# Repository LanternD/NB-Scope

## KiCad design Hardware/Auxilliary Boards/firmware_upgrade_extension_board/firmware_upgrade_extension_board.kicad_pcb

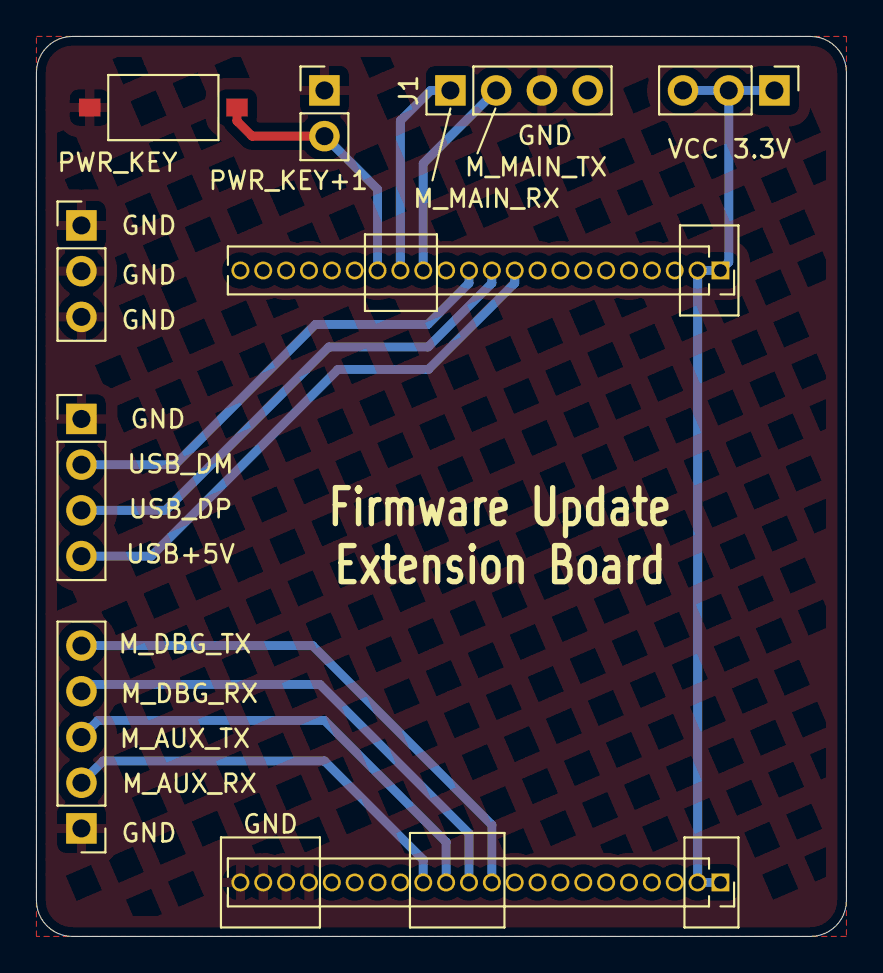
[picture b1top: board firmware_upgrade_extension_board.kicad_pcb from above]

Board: 2 copper layers, 45.0 x 50.0 mm, 9 parts (0 on the bottom side), 12 nets.

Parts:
J1: MAIN_UART_CONN; PinHeader_1x04_P2.54mm_Vertical
J2: Left_Conn; PinSocket_1x22_P1.27mm_Vertical
J3: Right_Conn; PinSocket_1x22_P1.27mm_Vertical
J4: PWR_KEY_TO_GND_CONN; PinHeader_1x02_P2.54mm_Vertical
J5: VCC_CONN; PinHeader_1x03_P2.54mm_Vertical
J6: GND_CONN; PinHeader_1x03_P2.54mm_Vertical
J7: DBG_UART_CONN; PinHeader_1x05_P2.54mm_Vertical
J8: USB_CONN; PinHeader_1x04_P2.54mm_Vertical
SW1: PWR_KEY_TO_GND_BTN; SMD_Switch

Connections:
+3V3: J2.1, J2.2, J3.1, J3.2, J5.1, J5.2, J5.3
/M_AUX_UART_Rx: J3.14, J7.2
/M_AUX_UART_Tx: J3.13, J7.3
/M_DBG_UART_Rx: J3.12, J7.4
/M_DBG_UART_TX: J3.11, J7.5
/M_MAIN_UART_Rx: J1.1, J2.15
/M_MAIN_UART_Tx: J1.2, J2.14
/M_PWRKEY: J2.16, J4.2, SW1.2
/M_USB_DM: J2.12, J8.2
/M_USB_DP: J2.11, J8.3
/M_USB_VBUS: J2.10, J8.4
GND: J1.3, J3.19, J3.20, J3.21, J3.22, J4.1, J6.1, J6.2, J6.3, J7.1, J8.1, SW1.1

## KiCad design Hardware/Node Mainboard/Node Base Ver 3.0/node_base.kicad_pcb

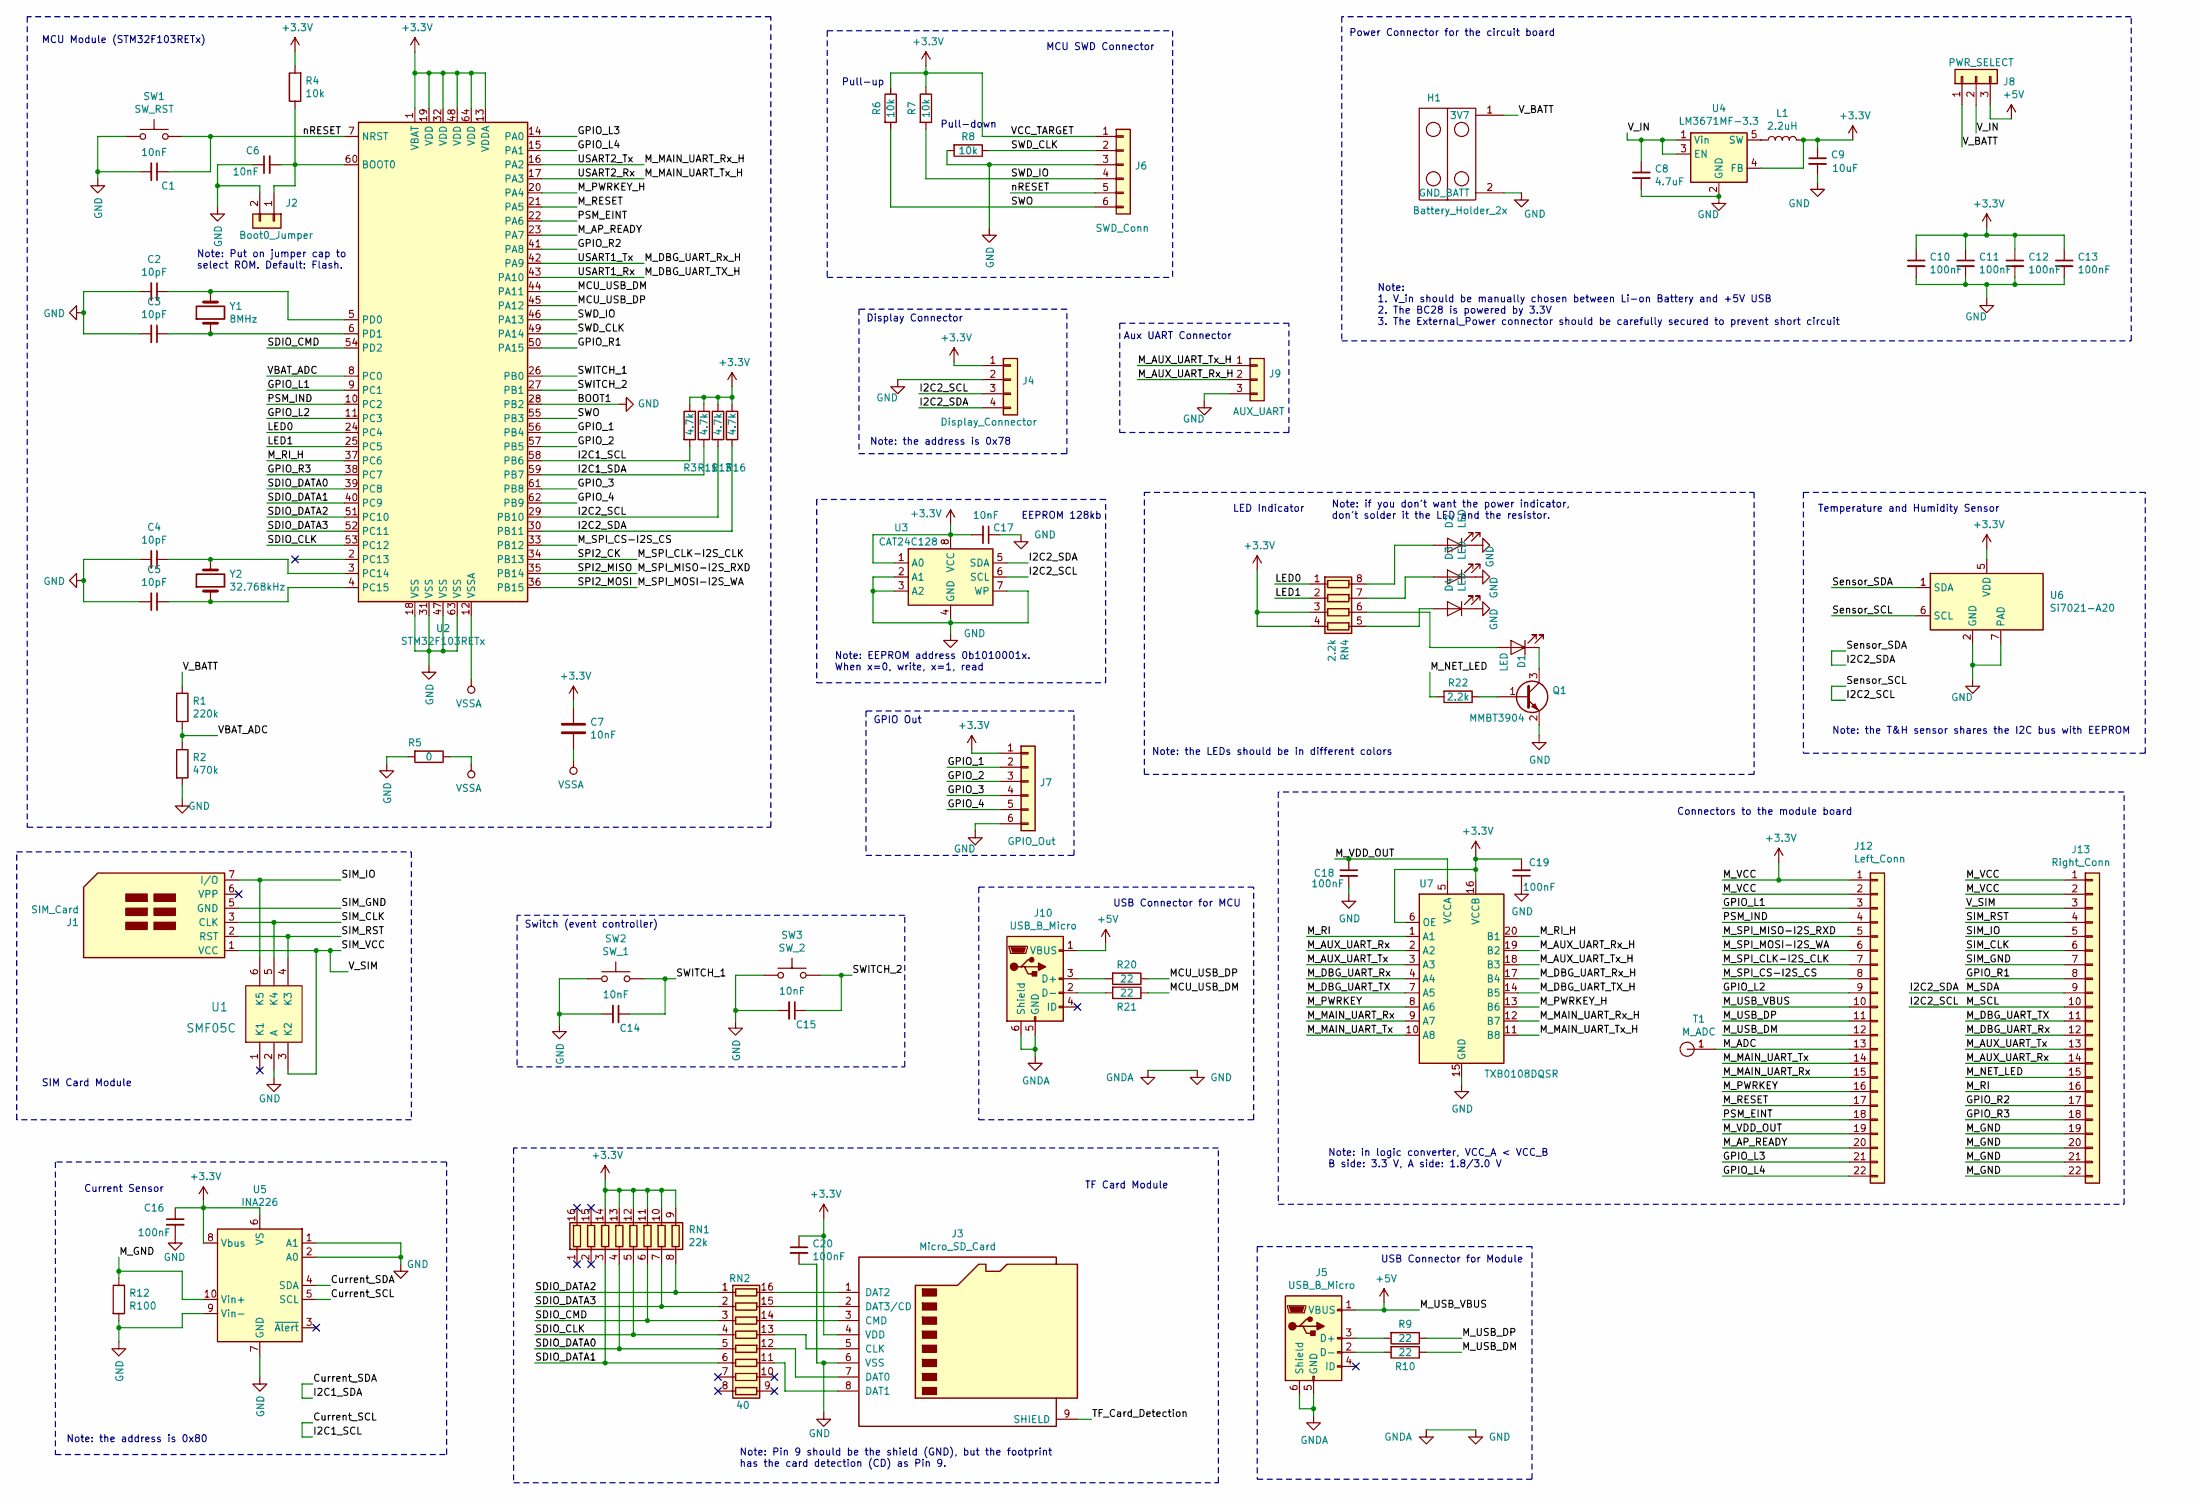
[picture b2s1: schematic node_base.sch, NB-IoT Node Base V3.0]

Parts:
C1, C6, C7, C14, C15, C17: 10nF; C_0603_1608Metric
C2, C3, C4, C5: 10pF; C_0603_1608Metric
C8: 4.7uF; C_1210_3225Metric
C9: 10uF; CP_Elec_4x5.4
C10, C11, C12, C13, C16, C18, C19, C20: 100nF; C_0603_1608Metric
D1, D2, D3, D4: LED; LED_0805_2012Metric
H1: Battery_Holder_2x; 18650_Battery_Holder_2x
J1: SIM_Card; Nano Sim Socket 1.1H, 6P
J2: Boot0_Jumper; PinHeader_1x02_P1.27mm_Vertical
J3: Micro_SD_Card; TF_Card_Socket
J4: Display_Connector; PinSocket_1x04_P1.27mm_Vertical
J5, J10: USB_B_Micro; USB_Micro-B_Molex-105017-0001
J6: SWD_Conn; PinSocket_1x06_P1.27mm_Vertical
J7: GPIO_Out; PinSocket_1x06_P1.27mm_Vertical
J8: PWR_SELECT; PinHeader_1x03_P2.54mm_Vertical
J9: AUX_UART; PinSocket_1x03_P1.27mm_Vertical
J12: Left_Conn; PinHeader_1x22_P1.27mm_Vertical
J13: Right_Conn; PinHeader_1x22_P1.27mm_Vertical
L1: 2.2uH; L_7.3x7.3_H4.5
Q1: MMBT3904; SOT-23
R1: 220k; R_0603_1608Metric
R2: 470k; R_0603_1608Metric
R3, R11, R13, R16: 4.7k; R_0603_1608Metric
R4, R6, R7, R8: 10k; R_0603_1608Metric
R5: 0; R_0603_1608Metric
R9, R10, R20, R21: 22; R_0603_1608Metric
R12: R100; R_1206_3216Metric
R22: 2.2k; R_0603_1608Metric_Pad1.05x0.95mm_HandSolder
RN1: 22k; R_Array_Convex_8x0602
RN2: 40; R_Array_Convex_8x0602
RN4: 2.2k; R_Array_Convex_4x0603
SW1: SW_RST; SW_SPST_FSMSM
SW2: SW_1; SW_SPST_FSMSM
SW3: SW_2; SW_SPST_FSMSM
T1: M_ADC; test_pad
U1: SMF05C
U2: STM32F103RETx; LQFP-64_10x10mm_P0.5mm
U3: CAT24C128; SOIC-8_3.9x4.9mm_P1.27mm
U4: LM3671MF-3.3; TSOT-23-5
U5: INA226; VSSOP-10_3x3mm_P0.5mm
U6: Si7021-A20; DFN-6-1EP_3x3mm_P1mm_EP1.5x2.4mm
U7: TXB0108DQSR; USON-20_2x4mm_P0.4mm
Y1: 8MHz; Crystal_SMD_5032-2Pin_5.0x3.2mm
Y2: 32.768kHz; Crystal_SMD_3215-2Pin_3.2x1.5mm

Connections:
+3V3: C7.1, C9.1, C10.1, C11.1, C12.1, C13.1, C16.1, C17.2, C19.2, C20.1, J3.4 (VDD), J4.1, J6.1, J7.1, J12.1, J12.2, J13.1, J13.2, L1.2, R3.1, R4.2, R6.1, R7.1, R11.1, R13.1, R16.1, RN1.9 (R8.2), RN1.10 (R7.2), RN1.11 (R6.2), RN1.12 (R5.2), RN1.13 (R4.2), RN1.14 (R3.2), RN4.3 (R3.1), RN4.4 (R4.1), U2.1 (VBAT), U2.13 (VDDA), U2.19 (VDD), U2.32 (VDD), U2.48 (VDD), U2.64 (VDD), U3.1 (A0), U3.8 (VCC), U4.4 (FB), U5.6 (VS), U5.8 (Vbus), U6.5 (VDD), U7.6 (OE), U7.16 (VCCB)
+5V: J5.1 (VBUS), J8.3, J10.1 (VBUS), J12.10
/Current_SCL: R3.2, U2.58 (PB6), U5.5 (SCL)
/Current_SDA: R11.2, U2.59 (PB7), U5.4 (SDA)
/GPIO_2: J7.3, U2.57 (PB5)
/GPIO_3: J7.4, U2.61 (PB8)
/GPIO_4: J7.5, U2.62 (PB9)
/GPIO_L1: J12.3, U2.9 (PC1)
/GPIO_L2: J12.9, U2.11 (PC3)
/GPIO_L3: J12.21, U2.14 (PA0)
/GPIO_L4: J12.22, U2.15 (PA1)
/GPIO_R1: J13.8, U2.50 (PA15)
/GPIO_R2: J13.17, U2.41 (PA8)
/GPIO_R3: J13.18, U2.38 (PC7)
/I2C2_SCL: J4.3, J13.10, R13.2, U2.29 (PB10), U3.6 (SCL), U6.6 (SCL)
/I2C2_SDA: J4.4, J13.9, R16.2, U2.30 (PB11), U3.5 (SDA), U6.1 (SDA)
/LED0: RN4.1 (R1.1), U2.24 (PC4)
/LED1: RN4.2 (R2.1), U2.25 (PC5)
/MCU_USB_DM: R21.1, U2.44 (PA11)
/MCU_USB_DP: R20.1, U2.45 (PA12)
/M_ADC: J12.13, T1.1
/M_AP_READY: J12.20, U2.23 (PA7)
/M_AUX_UART_Rx: J13.14, U7.2 (A2)
/M_AUX_UART_Rx_H: J9.2, U7.19 (B2)
/M_AUX_UART_Tx: J13.13, U7.3 (A3)
/M_AUX_UART_Tx_H: J9.1, U7.18 (B3)
/M_DBG_UART_Rx: J13.12, U7.4 (A4)
/M_DBG_UART_Rx_H: U2.42 (PA9), U7.17 (B4)
/M_DBG_UART_TX: J13.11, U7.7 (A5)
/M_DBG_UART_TX_H: U2.43 (PA10), U7.14 (B5)
/M_GND: J13.19, J13.20, J13.21, J13.22, R12.1, U5.10 (Vin+)
/M_MAIN_UART_Rx: J12.15, U7.9 (A7)
/M_MAIN_UART_Rx_H: U2.16 (PA2), U7.12 (B7)
/M_MAIN_UART_Tx: J12.14, U7.10 (A8)
/M_MAIN_UART_Tx_H: U2.17 (PA3), U7.11 (B8)
/M_NET_LED: J13.15, R22.2
/M_PWRKEY: J12.16, U7.8 (A6)
/M_PWRKEY_H: U2.20 (PA4), U7.13 (B6)
/M_RESET: J12.17, U2.21 (PA5)
/M_RI: J13.16, U7.1 (A1)
/M_RI_H: U2.37 (PC6), U7.20 (B1)
/M_SPI_CLK-I2S_CLK: J12.7, U2.34 (PB13)
/M_SPI_CS-I2S_CS: J12.8, U2.33 (PB12)
/M_SPI_MISO-I2S_RXD: J12.5, U2.35 (PB14)
/M_SPI_MOSI-I2S_WA: J12.6, U2.36 (PB15)
/M_USB_DM: J12.12, R10.1
/M_USB_DP: J12.11, R9.1
/M_VDD_OUT: C18.1, J12.19, U7.5 (VCCA)
/PSM_EINT: J12.18, U2.22 (PA6)
/PSM_IND: J12.4, U2.10 (PC2)
/SDIO_CLK: RN1.5 (R5.1), RN2.4 (R4.1), U2.53 (PC12)
/SDIO_CMD: RN1.6 (R6.1), RN2.3 (R3.1), U2.54 (PD2)
/SDIO_DATA0: RN1.4 (R4.1), RN2.5 (R5.1), U2.39 (PC8)
/SDIO_DATA1: RN1.3 (R3.1), RN2.6 (R6.1), U2.40 (PC9)
/SDIO_DATA2: RN1.8 (R8.1), RN2.1 (R1.1), U2.51 (PC10)
/SDIO_DATA3: RN1.7 (R7.1), RN2.2 (R2.1), U2.52 (PC11)
/SIM_CLK: J1.3 (CLK), J13.6, U1.5 (K4)
/SIM_GND: J1.5 (GND), J13.7
/SIM_IO: J1.7 (I/O), J13.5, U1.6 (K5)
/SIM_RST: J1.2 (RST), J13.4, U1.4 (K3)
/SIM_VCC: J1.1 (VCC), J13.3, U1.3 (K2)
/SWD_CLK: J6.2, R8.1, U2.49 (PA14)
/SWD_IO: J6.4, R7.2, U2.46 (PA13)
/SWITCH_1: C14.1, SW2.2, U2.26 (PB0)
/SWITCH_2: C15.1, SW3.2, U2.27 (PB1)
/SWO: J6.6, R6.2, U2.55 (PB3)
/VBAT_ADC: R1.2, R2.1, U2.8 (PC0)
/V_BATT: H1.1 (3V7), J8.1, R1.1
/V_IN: C8.1, J8.2, U4.1 (Vin), U4.3 (EN)
/nRESET: C1.1, J6.5, SW1.2, U2.7 (NRST)
GND: C1.2, C2.2, C3.2, C4.2, C5.2, C6.1, C8.2, C9.2, C10.2, C11.2, C12.2, C13.2, C14.2, C15.2, C16.2, C17.1, C18.2, C19.1, C20.2, D2.1 (K), D3.1 (K), D4.1 (K), H1.2 (GND_BATT), J2.2, J3.6 (VSS), J4.2, J5.5 (GND), J5.6 (Shield), J6.3, J7.6, J9.3, J10.5 (GND), J10.6 (Shield), Q1.2 (E), R2.2, R5.2, R8.2, R12.2, SW1.1, SW2.1, SW3.1, U1.2 (A), U2.18 (VSS), U2.28 (PB2), U2.31 (VSS), U2.47 (VSS), U2.63 (VSS), U3.2 (A1), U3.3 (A2), U3.4 (GND), U3.7 (WP), U4.2 (GND), U5.1 (A1), U5.2 (A0), U5.7 (GND), U5.9 (Vin-), U6.2 (GND), U6.7 (PAD), U7.15 (GND)
unnamed: C2.1, U2.5 (PD0), Y1.2
unnamed: C3.1, U2.6 (PD1), Y1.1
unnamed: C4.1, U2.3 (PC14), Y2.2
unnamed: C5.1, U2.4 (PC15), Y2.1
unnamed: C6.2, J2.1, R4.1, U2.60 (BOOT0)
unnamed: D1.1 (K), Q1.3 (C)
unnamed: D1.2 (A), RN4.6 (R3.2)
unnamed: D2.2 (A), RN4.8 (R1.2)
unnamed: D3.2 (A), RN4.7 (R2.2)
unnamed: D4.2 (A), RN4.5 (R4.2)
unnamed: J3.1 (DAT2), RN2.16 (R1.2)
unnamed: J3.2 (DAT3/CD), RN2.15 (R2.2)
unnamed: J3.3 (CMD), RN2.14 (R3.2)
unnamed: J3.5 (CLK), RN2.13 (R4.2)
unnamed: J3.7 (DAT0), RN2.12 (R5.2)
unnamed: J3.8 (DAT1), RN2.11 (R6.2)
unnamed: J5.2 (D-), R10.2
unnamed: J5.3 (D+), R9.2
unnamed: J10.2 (D-), R21.2
unnamed: J10.3 (D+), R20.2
unnamed: L1.1, U4.5 (SW)
unnamed: Q1.1 (B), R22.1
VSSA: C7.2, R5.1, U2.12 (VSSA)

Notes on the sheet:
Note: Put on jumper cap to select ROM. Default: Flash.
MCU Module (STM32F103RETx)
Power Connector for the circuit board
Note: 1. V_in should be manually chosen between Li-on Battery and +5V USB 2. The BC28 is powered by 3.3V 3. The External_Power connector should be carefully secured to prevent short circuit
Pull-down
Pull-up
MCU SWD Connector
EEPROM 128kb
Note: the LEDs should be in different colors
LED Indicator
Note: if you don’t want the power indicator, don’t solder it the LED and the resistor.
Note: the T&H sensor shares the I2C bus with EEPROM
Connectors to the module board
Current Sensor
SIM Card Module
Temperature and Humidity Sensor
Switch (event controller)
Note: Pin 9 should be the shield (GND), but the footprint has the card detection (CD) as Pin 9.
TF Card Module
Note: EEPROM address 0b1010001x. When x=0, write, x=1, read
Display Connector
Note: the address is 0x78
Note: the address is 0x80
Aux UART Connector
USB Connector for MCU
USB Connector for Module
GPIO Out
Note: in logic converter, VCC_A < VCC_B B side: 3.3 V, A side: 1.8/3.0 V

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
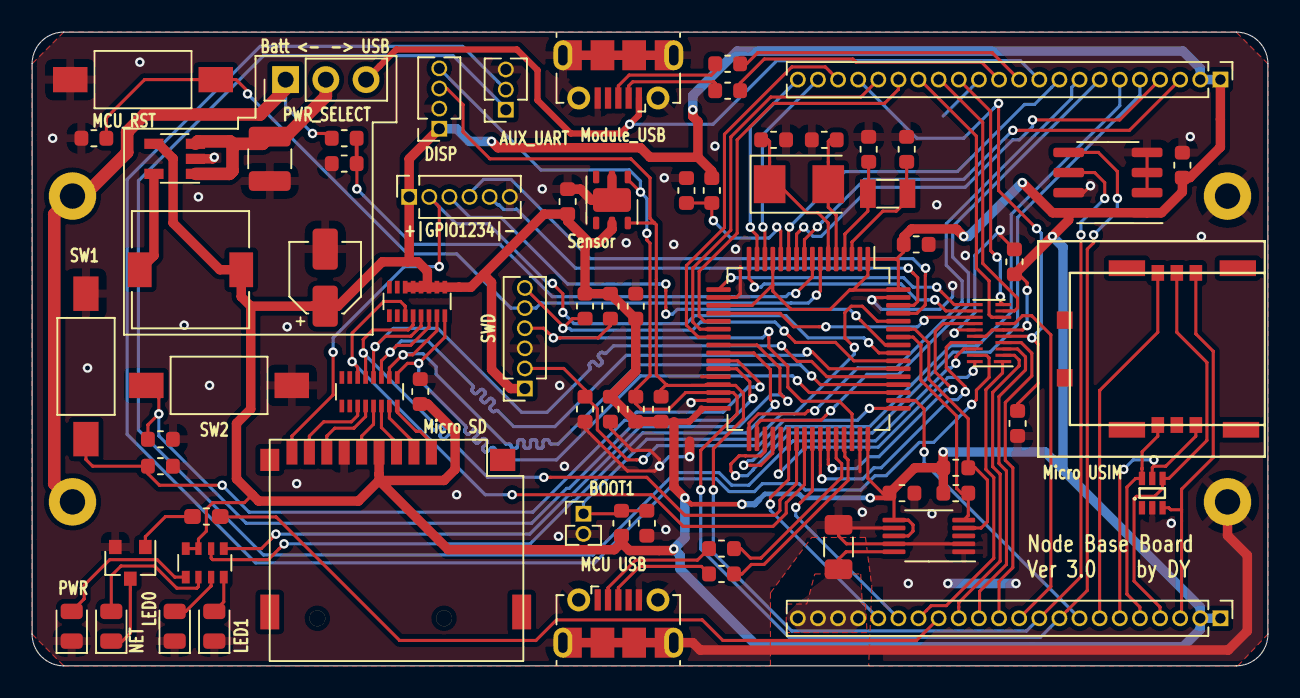
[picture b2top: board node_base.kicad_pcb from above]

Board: 2 copper layers, 78.0 x 40.0 mm, 72 parts (1 on the bottom side), 95 nets.

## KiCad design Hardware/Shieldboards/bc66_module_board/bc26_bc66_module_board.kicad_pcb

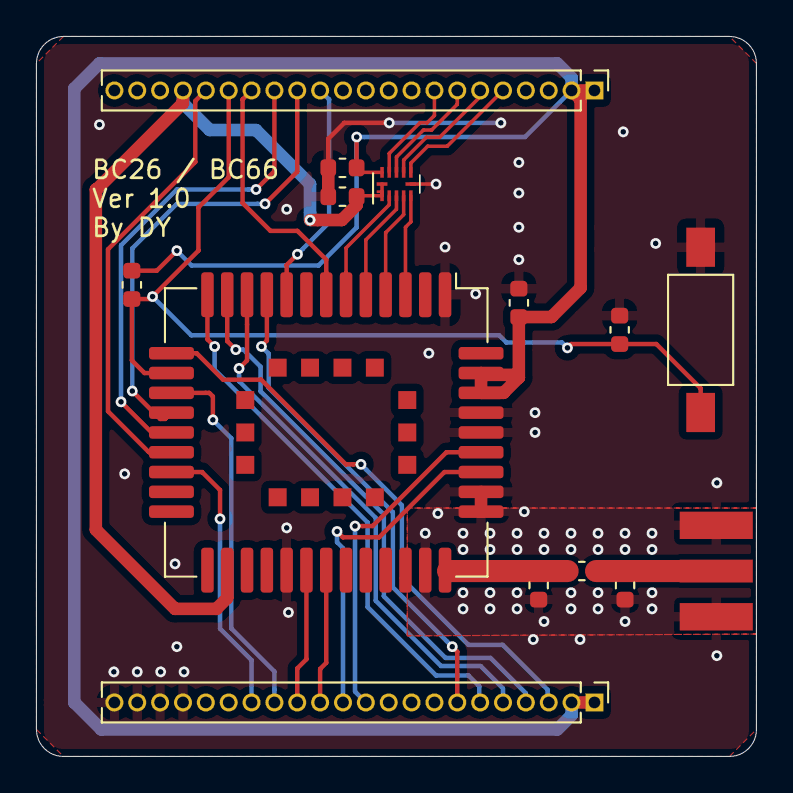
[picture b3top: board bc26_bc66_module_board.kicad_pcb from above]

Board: 2 copper layers, 40.0 x 40.0 mm, 14 parts (0 on the bottom side), 30 nets.

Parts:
C1, C2, C3, C4, C5, C7: 100nF; C_0603_1608Metric
J1: 1865; SMA_Antenna
J12: Left_Conn; PinHeader_1x22_P1.27mm_Vertical
J13: Right_Conn; PinHeader_1x22_P1.27mm_Vertical
R1: 0; R_0603_1608Metric
R11: 10k; R_0603_1608Metric
SW2: SW_Push; SW_SPST_FSMSM
U1: BC66; Quectel_BC66
U2: TXB0304RUT; Texas_R_PUQFN-N12

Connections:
+3V3: C1.1, C5.1, J12.1, J12.2, J13.1, J13.2, R11.2, U1.42, U1.43, U2.11
/B_SPI_CLK-I2S_CLK: J12.7, U2.9
/B_SPI_CS-I2S_CS: J12.8, U2.10
/B_SPI_MISO-I2S_RXD: J12.5, U2.7
/B_SPI_MOSI-I2S_WA: J12.6, U2.8
/M_ADC: J12.13, U1.9
/M_AUX_UART_Rx: J13.14, U1.28
/M_AUX_UART_Tx: J13.13, U1.29
/M_DBG_UART_Rx: J13.12, U1.38
/M_DBG_UART_TX: J13.11, U1.39
/M_MAIN_UART_Rx: J12.15, U1.18
/M_MAIN_UART_Tx: J12.14, U1.17
/M_NET_LED: J13.15, U1.16
/M_PWRKEY: J12.16, U1.7
/M_RESET: C7.1, J12.17, R11.1, SW2.2, U1.15
/M_RI: J13.16, U1.20
/M_SPI_CLK-I2S_CLK: U1.5, U2.3
/M_SPI_CS-I2S_CS: U1.6, U2.2
/M_SPI_MISO-I2S_RXD: U1.3, U2.5
/M_SPI_MOSI-I2S_WA: U1.4, U2.4
/M_VDD_OUT: C4.1, J12.19, U1.24, U2.1, U2.12
/PSM_EINT: J12.18, U1.19
/SIM_CLK: J13.6, U1.13
/SIM_GND: J13.7, U1.10
/SIM_IO: J13.5, U1.11
/SIM_RST: J13.4, U1.12
/V_SIM: J13.3, U1.14
GND: C1.2, C2.2, C3.2, C4.2, C5.2, C7.2, J1.GND1, J1.GND2, J1.GND3, J1.GND4, J13.19, J13.20, J13.21, J13.22, SW2.1, U1.1, U1.27, U1.34, U1.36, U1.37, U1.40, U1.41, U2.6
unnamed: C2.1, R1.2, U1.35
unnamed: C3.1, J1.P, R1.1

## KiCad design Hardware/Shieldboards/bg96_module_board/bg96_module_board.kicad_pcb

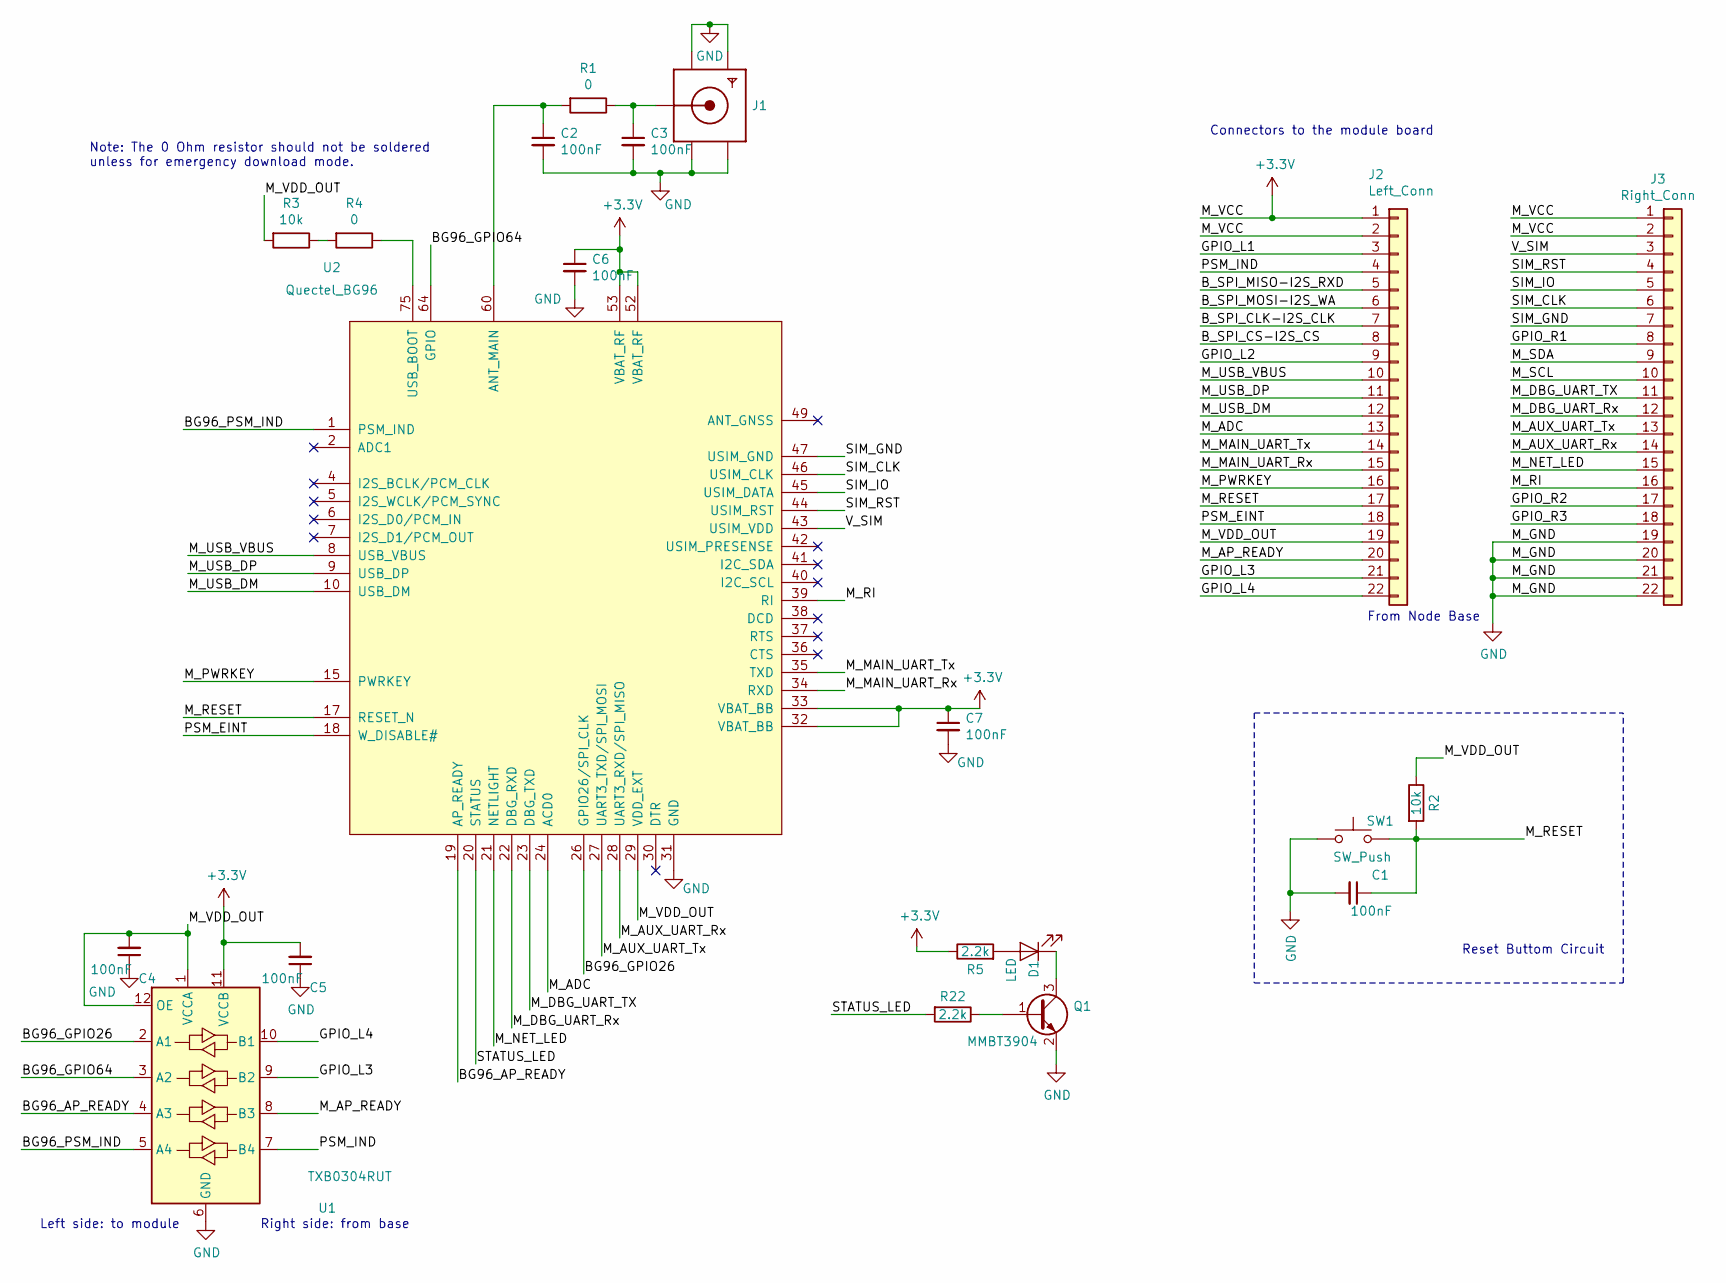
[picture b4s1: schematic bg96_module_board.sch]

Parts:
C1, C2, C3, C4, C5, C6, C7: 100nF; C_0603_1608Metric
D1: LED; LED_0805_2012Metric
J1: 1865; SMA_Antenna
J2: Left_Conn; PinHeader_1x22_P1.27mm_Vertical
J3: Right_Conn; PinHeader_1x22_P1.27mm_Vertical
Q1: MMBT3904; SOT-23
R1, R4: 0; R_0603_1608Metric
R2, R3: 10k; R_0603_1608Metric
R5, R22: 2.2k; R_0603_1608Metric
SW1: SW_Push; SW_SPST_FSMSM
U1: TXB0304RUT; Texas_R_PUQFN-N12
U2: Quectel_BG96

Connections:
+3V3: C5.2, C6.1, C7.1, J2.1, J2.2, J3.1, J3.2, R5.1, U1.11 (VCCB), U2.32 (VBAT_BB), U2.33 (VBAT_BB), U2.52 (VBAT_RF), U2.53 (VBAT_RF)
/BG96_AP_READY: U1.4 (A3), U2.19 (AP_READY)
/BG96_GPIO26: U1.2 (A1), U2.26 (GPIO26/SPI_CLK)
/BG96_GPIO64: U1.3 (A2), U2.64 (GPIO)
/BG96_PSM_IND: U1.5 (A4), U2.1 (PSM_IND)
/B_SPI_CLK-I2S_CLK: J2.7
/B_SPI_CS-I2S_CS: J2.8
/B_SPI_MISO-I2S_RXD: J2.5
/B_SPI_MOSI-I2S_WA: J2.6
/GPIO_L1: J2.3
/GPIO_L2: J2.9
/GPIO_L3: J2.21, U1.9 (B2)
/GPIO_L4: J2.22, U1.10 (B1)
/GPIO_R1: J3.8
/GPIO_R2: J3.17
/GPIO_R3: J3.18
/M_ADC: J2.13, U2.24 (ACD0)
/M_AP_READY: J2.20, U1.8 (B3)
/M_AUX_UART_Rx: J3.14, U2.28 (UART3_RXD/SPI_MISO)
/M_AUX_UART_Tx: J3.13, U2.27 (UART3_TXD/SPI_MOSI)
/M_DBG_UART_Rx: J3.12, U2.22 (DBG_RXD)
/M_DBG_UART_TX: J3.11, U2.23 (DBG_TXD)
/M_MAIN_UART_Rx: J2.15, U2.34 (RXD)
/M_MAIN_UART_Tx: J2.14, U2.35 (TXD)
/M_NET_LED: J3.15, U2.21 (NETLIGHT)
/M_PWRKEY: J2.16, U2.15 (PWRKEY)
/M_RESET: C1.1, J2.17, R2.2, SW1.2, U2.17 (RESET_N)
/M_RI: J3.16, U2.39 (RI)
/M_SCL: J3.10
/M_SDA: J3.9
/M_USB_DM: J2.12, U2.10 (USB_DM)
/M_USB_DP: J2.11, U2.9 (USB_DP)
/M_USB_VBUS: J2.10, U2.8 (USB_VBUS)
/M_VDD_OUT: C4.2, J2.19, R2.1, R3.2, U1.1 (VCCA), U1.12 (OE), U2.29 (VDD_EXT)
/PSM_EINT: J2.18, U2.18 (W_DISABLE#)
/PSM_IND: J2.4, U1.7 (B4)
/SIM_CLK: J3.6, U2.46 (USIM_CLK)
/SIM_GND: J3.7, U2.47 (USIM_GND)
/SIM_IO: J3.5, U2.45 (USIM_DATA)
/SIM_RST: J3.4, U2.44 (USIM_RST)
/STATUS_LED: R22.2, U2.20 (STATUS)
/V_SIM: J3.3, U2.43 (USIM_VDD)
GND: C1.2, C2.2, C3.2, C4.1, C5.1, C6.2, C7.2, J1.GND1, J1.GND2, J1.GND3, J1.GND4, J3.19, J3.20, J3.21, J3.22, Q1.2 (E), SW1.1, U1.6 (GND), U2.3 (GND), U2.31 (GND), U2.48 (GND), U2.50 (GND), U2.54 (GND), U2.55 (GND), U2.58 (GND), U2.59 (GND), U2.61 (GND), U2.62 (GND), U2.67 (GND), U2.68 (GND), U2.69 (GND), U2.70 (GND), U2.71 (GND), U2.72 (GND), U2.73 (GND), U2.74 (GND), U2.79 (GND), U2.80 (GND), U2.81 (GND), U2.82 (GND), U2.89 (GND), U2.90 (GND), U2.91 (GND), U2.100 (GND), U2.101 (GND), U2.102 (GND)
unnamed: C2.1, R1.2, U2.60 (ANT_MAIN)
unnamed: C3.1, J1.P, R1.1
unnamed: D1.1 (K), Q1.3 (C)
unnamed: D1.2 (A), R5.2
unnamed: Q1.1 (B), R22.1
unnamed: R3.1, R4.2
unnamed: R4.1, U2.75 (USB_BOOT)

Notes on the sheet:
Connectors to the module board
From Node Base
Reset Buttom Circuit
Right side: from base
Left side: to module
Note: The 0 Ohm resistor should not be soldered unless for emergency download mode.

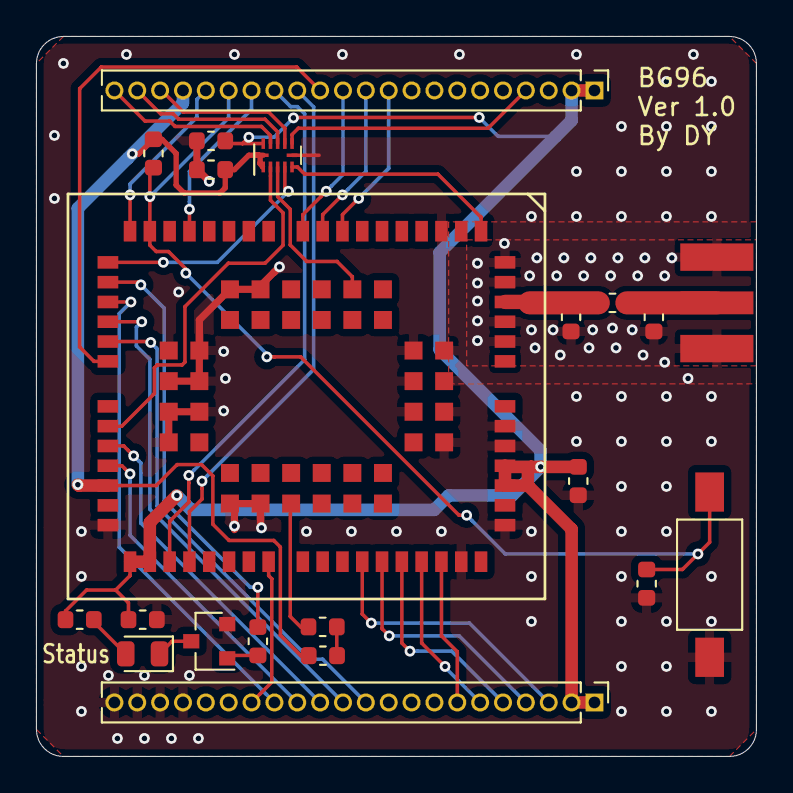
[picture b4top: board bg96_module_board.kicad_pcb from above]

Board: 2 copper layers, 40.0 x 40.0 mm, 21 parts (0 on the bottom side), 39 nets.
